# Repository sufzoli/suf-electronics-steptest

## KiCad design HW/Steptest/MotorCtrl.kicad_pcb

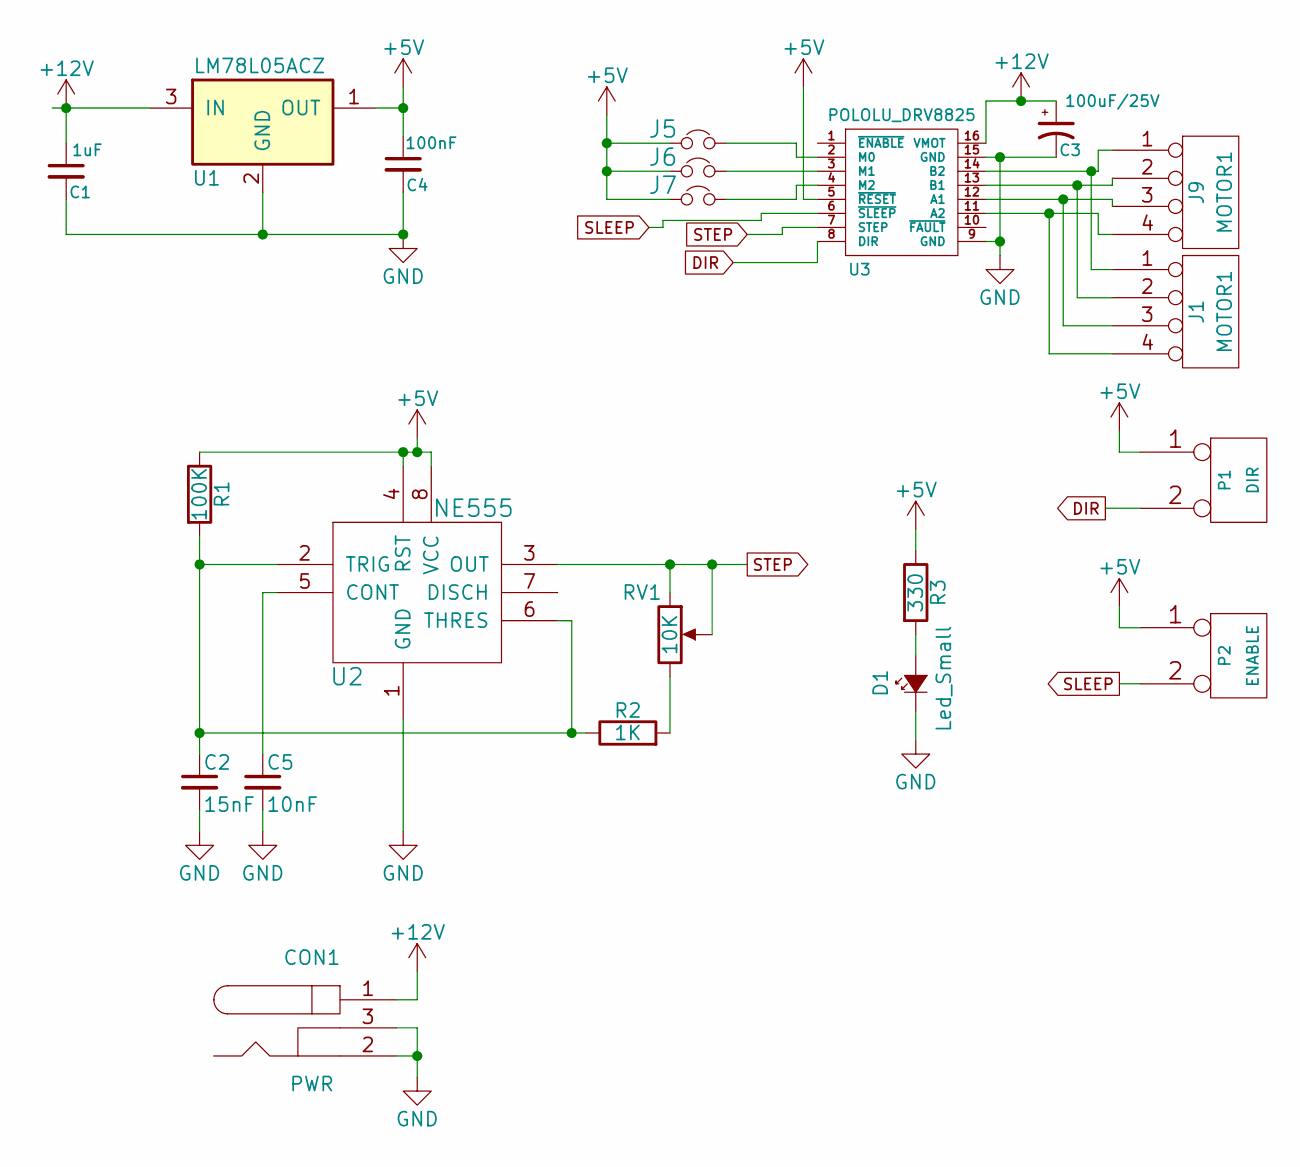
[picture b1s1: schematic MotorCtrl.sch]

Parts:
C1: 1uF; C_Disc_D3.0mm_W1.6mm_P2.50mm
C2: 15nF; C_Disc_D3.0mm_W1.6mm_P2.50mm
C3: 100uF/25V; CP_Radial_D10.0mm_P5.00mm
C4: 100nF; C_Disc_D3.0mm_W1.6mm_P2.50mm
C5: 10nF; C_Disc_D3.0mm_W1.6mm_P2.50mm
CON1: PWR; BARREL_JACK
D1: Led_Small; LED_D3.0mm_Horizontal_O3.81mm_Z10.0mm
J1, J9: MOTOR1; CONN_NCW254-04S
J5, J6, J7: Pin_Header_Straight_1x02_Pitch2.54mm
P1: DIR; CONN_NCW254-02S
P2: ENABLE; CONN_NCW254-02S
R1: 100K; R_Axial_DIN0207_L6.3mm_D2.5mm_P10.16mm_Horizontal
R2: 1K; R_Axial_DIN0207_L6.3mm_D2.5mm_P10.16mm_Horizontal
R3: 330; R_Axial_DIN0207_L6.3mm_D2.5mm_P10.16mm_Horizontal
RV1: 10K; Potentiometer_Alps_RK163_Single_Vertical
U1: LM78L05ACZ; TO-92_Molded_Wide
U2: NE555; DIP-8_W7.62mm_LongPads
U3: POLOLU_DRV8825; POLOLU_STEPPER

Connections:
+5V: C4.1, J5.1, J6.1, J7.1, P1.1, P2.1, R1.1, R3.1, U1.1 (OUT), U2.4 (RST), U2.8 (VCC), U3.5 (~RESET)
+12V: C1.1, C3.1, CON1.1, U1.3 (IN), U3.16 (VMOT)
DIR: P1.2 (PM), U3.8 (DIR)
GND: C1.2, C2.2, C3.2, C4.2, C5.2, CON1.2, CON1.3, D1.1 (K), U1.2 (GND), U2.1 (GND), U3.9 (GND), U3.15 (GND)
unnamed: C2.1, R1.2, R2.1, U2.2 (TRIG), U2.6 (THRES)
unnamed: C5.1, U2.5 (CONT)
unnamed: D1.2 (A), R3.2
unnamed: J1.1, J9.1, U3.14 (B2)
unnamed: J1.2, J9.2, U3.13 (B1)
unnamed: J1.3, J9.3, U3.12 (A1)
unnamed: J1.4, J9.4, U3.11 (A2)
unnamed: J5.2, U3.2 (M0)
unnamed: J6.2, U3.3 (M1)
unnamed: J7.2, U3.4 (M2)
unnamed: R2.2, RV1.3
SLEEP: P2.2 (PM), U3.6 (~SLEEP)
STEP: RV1.1, RV1.2, U2.3 (OUT), U3.7 (STEP)

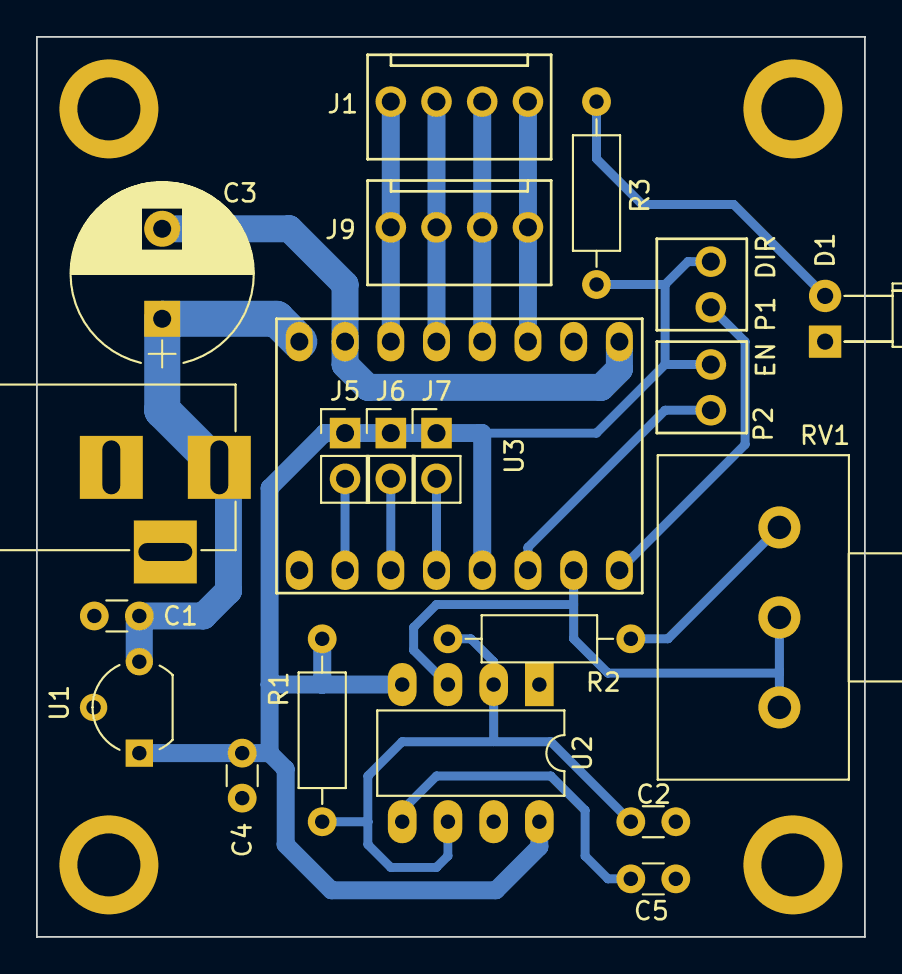
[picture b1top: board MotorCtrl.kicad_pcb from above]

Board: 2 copper layers, 46.0 x 50.0 mm, 25 parts (0 on the bottom side), 17 nets.

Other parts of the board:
MNT_HOLE_3.5, MNT_HOLE_3.5#2, MNT_HOLE_3.5#3, MNT_HOLE_3.5#4: Val**; MNT_HOLE_3.5

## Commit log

2021-03-20 Add Toshiba TB6600 datasheet
